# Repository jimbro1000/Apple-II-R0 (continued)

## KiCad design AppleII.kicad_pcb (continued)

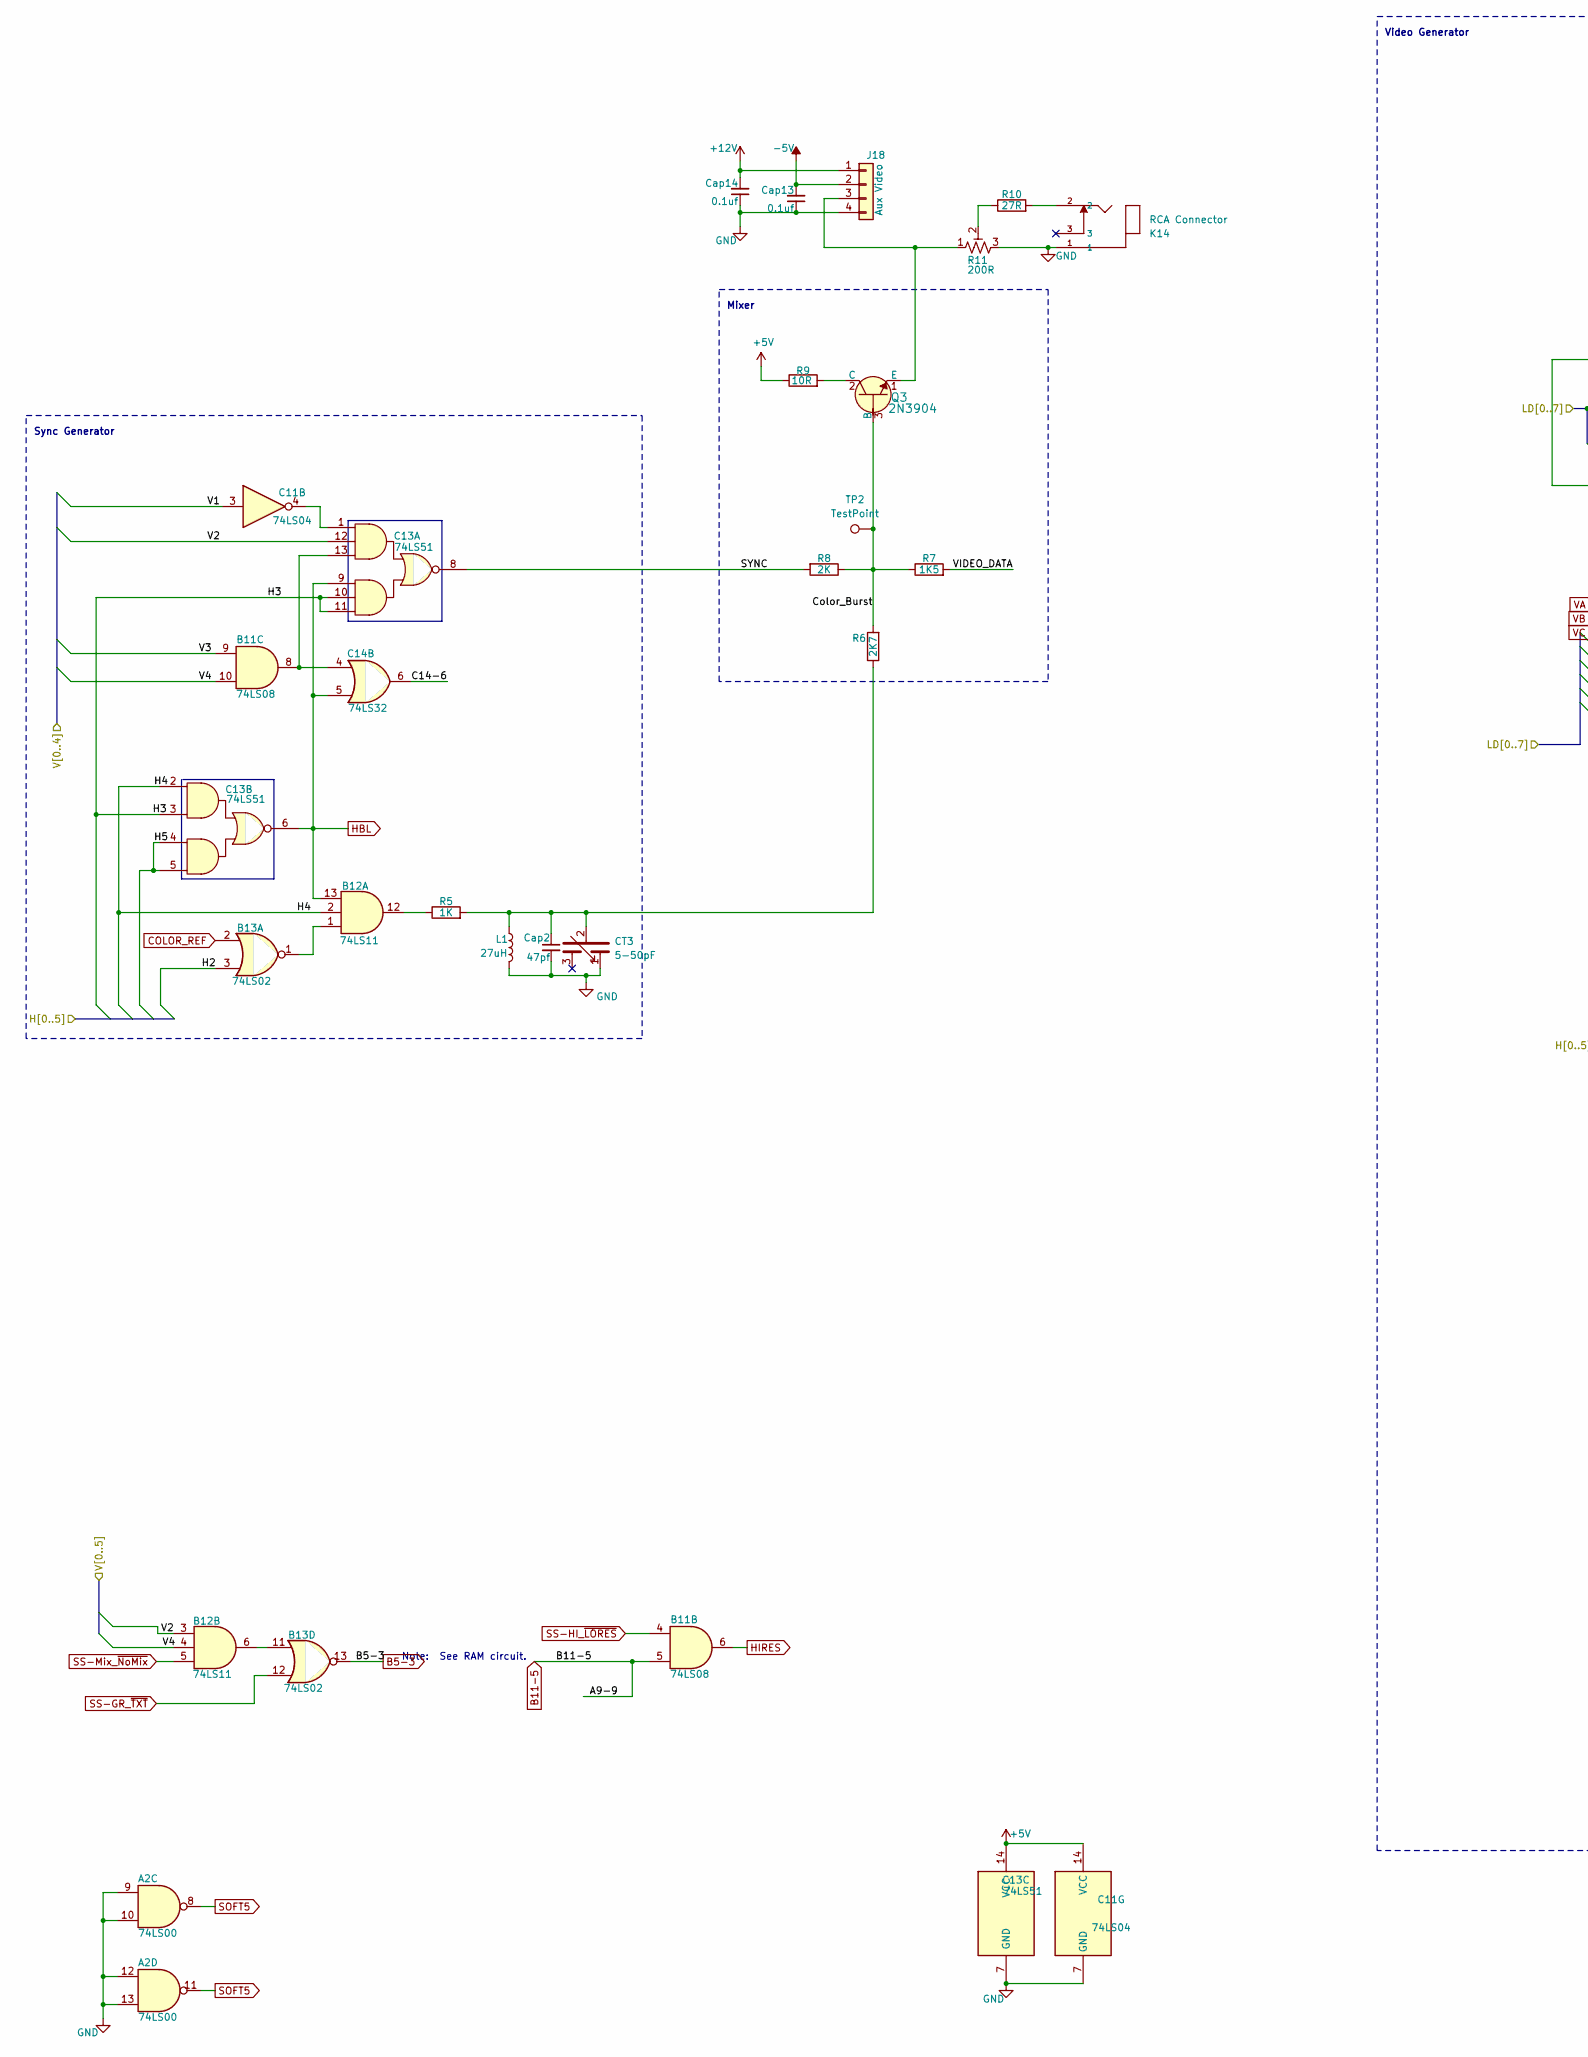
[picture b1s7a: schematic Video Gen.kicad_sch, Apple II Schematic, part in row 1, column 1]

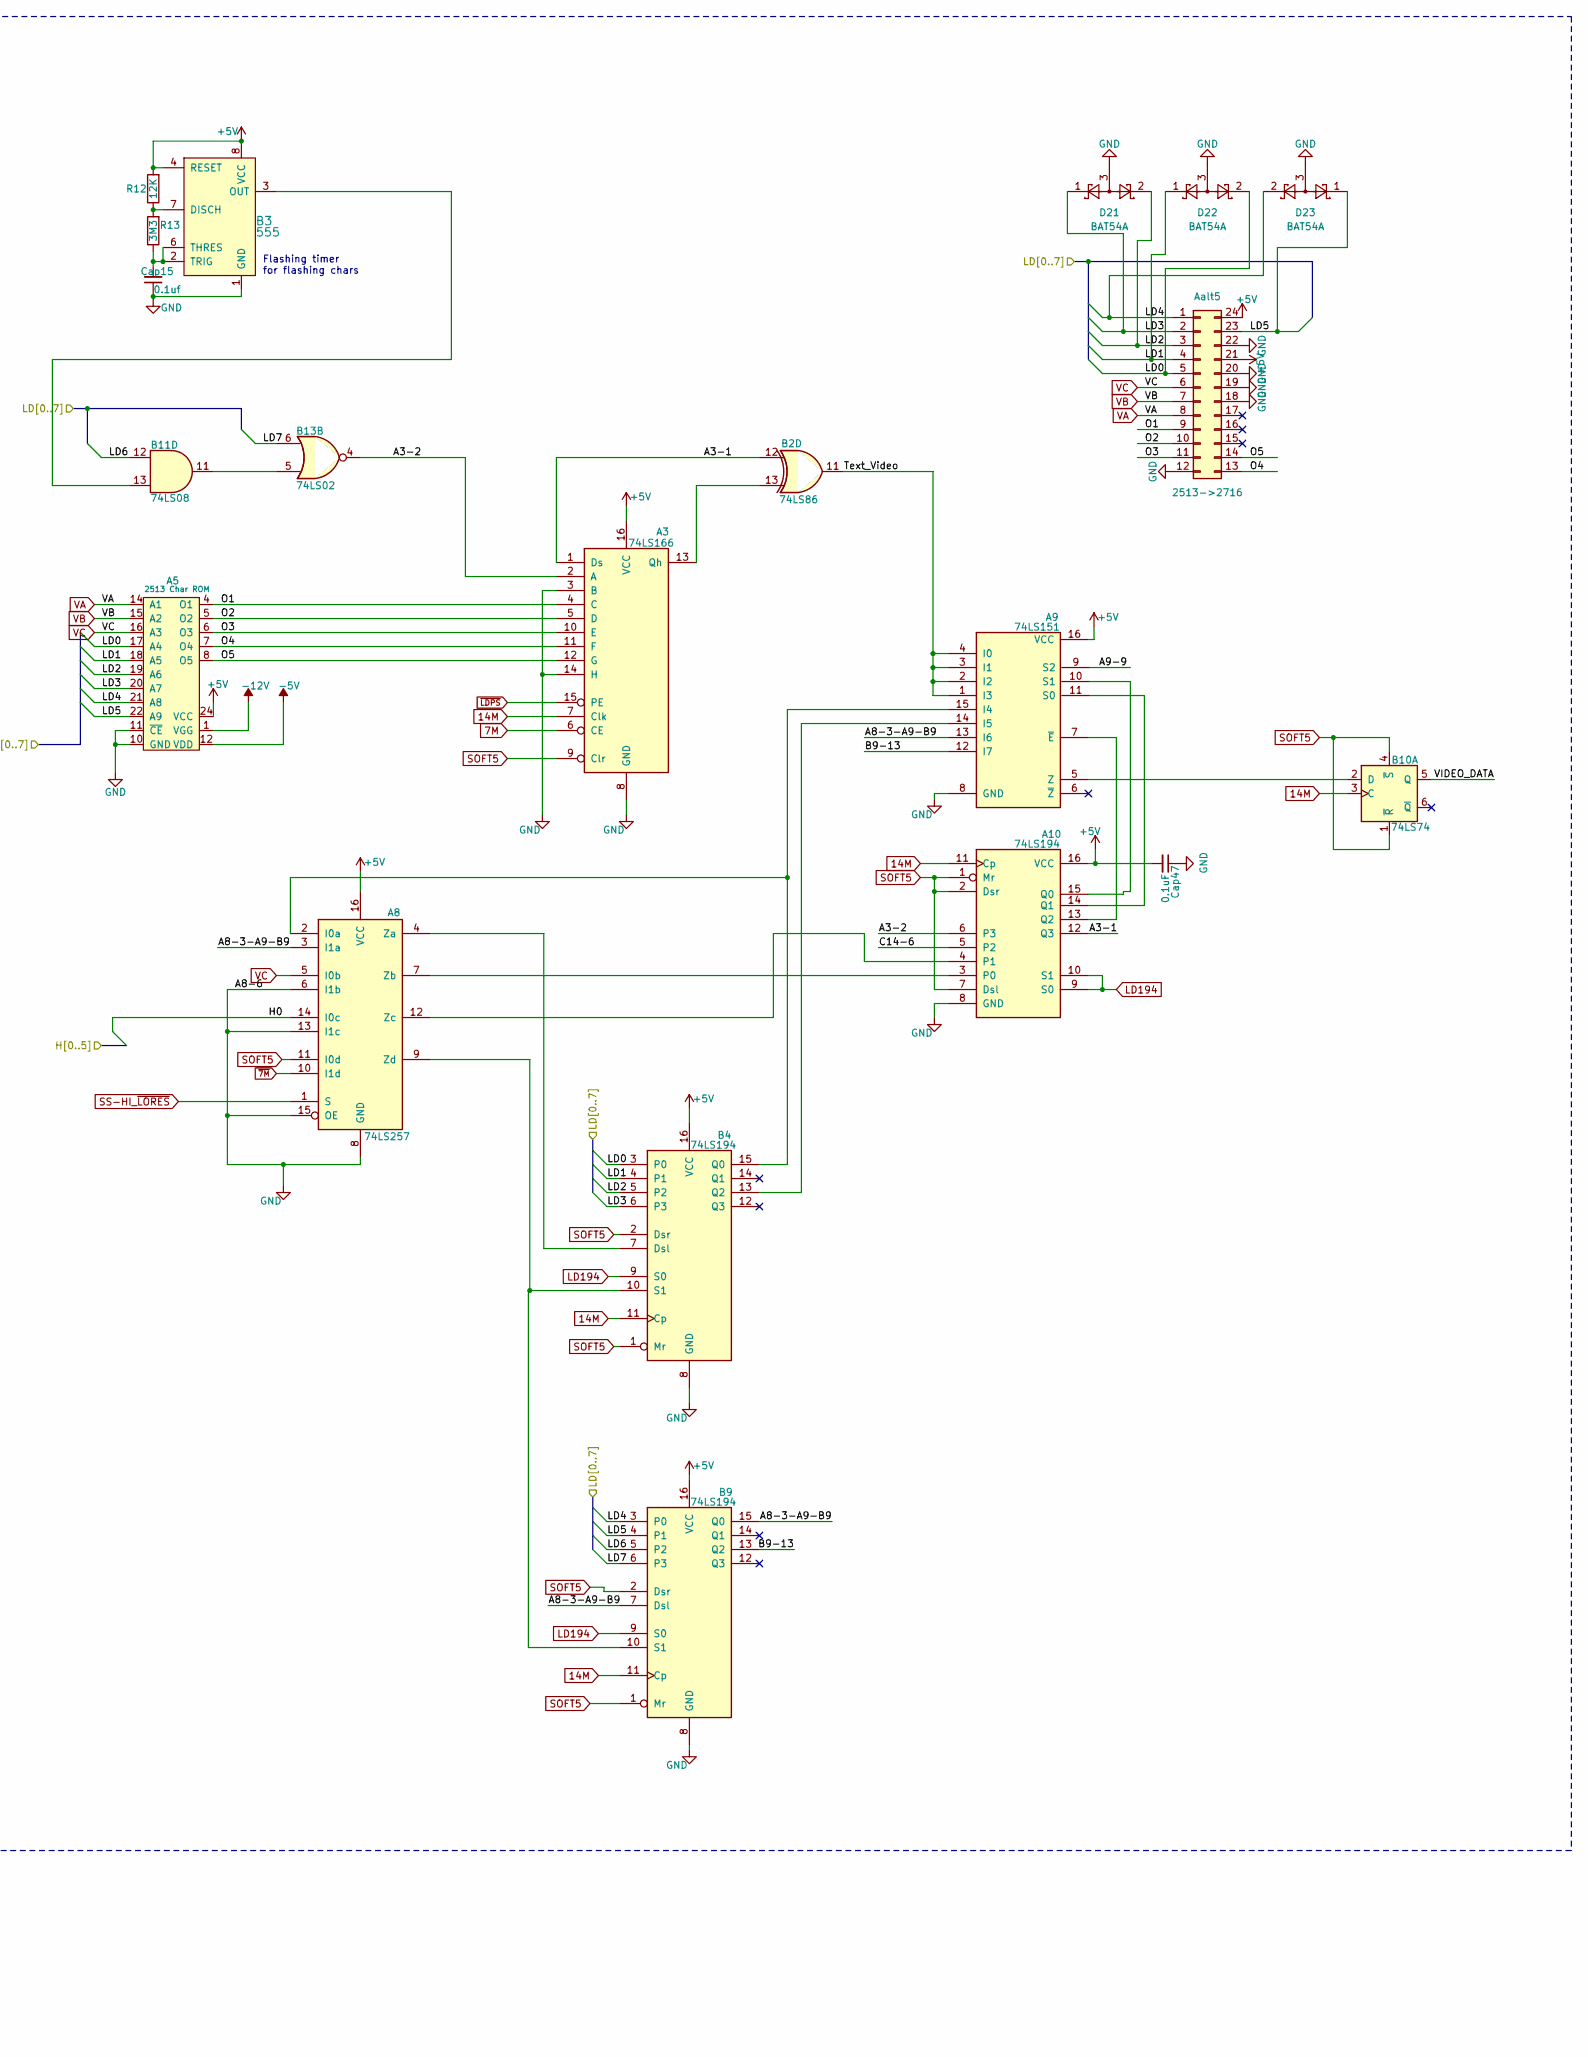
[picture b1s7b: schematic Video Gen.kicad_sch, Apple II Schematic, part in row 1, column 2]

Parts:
A2: 74LS00; DIP-14_W7.62mm
A3: 74LS166; DIP-16_W7.62mm
A5: 2513 Char ROM; DIP-24_W15.24mm
A8: 74LS257; DIP-16_W7.62mm
A9: 74LS151; DIP-16_W7.62mm
A10: 74LS194; DIP-16_W7.62mm
Aalt5: 2513->2716; DIP-24_W15.24mm_Socket
B2: 74LS86; DIP-14_W7.62mm
B3: 555; DIP-8_W7.62mm; MPN NE555P; Digi-Key_PN 296-1411-5-ND
B4, B9: 74LS194; DIP-16_W7.62mm
B10: 74LS74; DIP-14_W7.62mm
B11: 74LS08; DIP-14_W7.62mm
B12: 74LS11; DIP-14_W7.62mm
B13: 74LS02; DIP-14_W7.62mm
C11: 74LS04; DIP-14_W7.62mm
C13: 74LS51; DIP-14_W7.62mm
C14: 74LS32; DIP-14_W7.62mm
CT3: 5-50pF; COLOUR_TRIM; DigiKey BFC280831659-ND
Cap2: 47pf; C_Disc_D7.0mm_W2.5mm_P5.00mm
Cap13, Cap14, Cap15: 0.1uf; C_Disc_D5.0mm_W2.5mm_P5.00mm
Cap47: 0.1uF; C_Disc_D5.0mm_W2.5mm_P5.00mm
D21, D22, D23: BAT54A; SOT-23
J18: Aux Video; PinHeader_1x04_P2.54mm_Vertical
K14: RCA Connector; VIDEO; DigiKey PJRAN1X1U03X-ND
L1: 27uH; L_Axial_L7.0mm_D3.3mm_P12.70mm_Horizontal_Fastron_MICC
Q3: 2N3904; TO-92; MPN 2N3904; Digi-Key_PN 2N3904CS-ND
R5: 1K; R_Axial_DIN0207_L6.3mm_D2.5mm_P10.16mm_Horizontal
R6: 2K7; R_Axial_DIN0207_L6.3mm_D2.5mm_P10.16mm_Horizontal
R7: 1K5; R_Axial_DIN0207_L6.3mm_D2.5mm_P10.16mm_Horizontal
R8: 2K; R_Axial_DIN0207_L6.3mm_D2.5mm_P10.16mm_Horizontal
R9: 10R; R_Axial_DIN0207_L6.3mm_D2.5mm_P10.16mm_Horizontal
R10: 27R; R_Axial_DIN0207_L6.3mm_D2.5mm_P10.16mm_Horizontal
R11: 200R; Potentiometer_Bourns_3266Y_Vertical
R12: 12K; R_Axial_DIN0207_L6.3mm_D2.5mm_P10.16mm_Horizontal
R13: 3M3; R_Axial_DIN0207_L6.3mm_D2.5mm_P10.16mm_Horizontal
TP2: TestPoint; TestPoint_THTPad_1.5x1.5mm_Drill0.7mm

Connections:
7M: A3.6 (CE); also elsewhere on the board
14M: A3.7 (Clk), A10.11 (Cp), B4.11 (Cp), B9.11 (Cp), B10.3 (C); also elsewhere on the board
+5V: A3.16 (VCC), A5.24 (VCC), A8.16 (VCC), A9.16 (VCC), A10.16 (VCC), Aalt5.21, Aalt5.24, B3.4 (RESET), B3.8 (VCC), B4.16 (VCC), B9.16 (VCC), C11.14 (VCC), C13.14 (VCC), Cap47.2, R9.1, R12.2; also elsewhere on the board
+12V: Cap14.2, J18.1; also elsewhere on the board
-5V: A5.12 (VDD), Cap13.2, J18.2; also elsewhere on the board
-12V: A5.1 (VGG); also elsewhere on the board
/CPU Tranceiver Driver and Data MUX/LD0: A5.17 (A4), Aalt5.5, B4.3 (P0), D22.2; also elsewhere on the board
/CPU Tranceiver Driver and Data MUX/LD1: A5.18 (A5), Aalt5.4, B4.4 (P1), D22.1; also elsewhere on the board
/CPU Tranceiver Driver and Data MUX/LD2: A5.19 (A6), Aalt5.3, B4.5 (P2), D21.2; also elsewhere on the board
/CPU Tranceiver Driver and Data MUX/LD3: A5.20 (A7), Aalt5.2, B4.6 (P3), D21.1; also elsewhere on the board
/CPU Tranceiver Driver and Data MUX/LD4: A5.21 (A8), Aalt5.1, B9.3 (P0), D23.2; also elsewhere on the board
/CPU Tranceiver Driver and Data MUX/LD5: A5.22 (A9), Aalt5.23, B9.4 (P1), D23.1; also elsewhere on the board
/CPU Tranceiver Driver and Data MUX/LD6: B9.5 (P2), B11.12; also elsewhere on the board
/CPU Tranceiver Driver and Data MUX/LD7: B9.6 (P3), B13.6; also elsewhere on the board
/Clock Generation/H0: A8.14 (I0c); also elsewhere on the board
/Clock Generation/H2: B13.3; also elsewhere on the board
/Clock Generation/H3: C13.3, C13.10, C13.11; also elsewhere on the board
/Clock Generation/H4: B12.2, C13.2; also elsewhere on the board
/Clock Generation/H5: C13.4, C13.5; also elsewhere on the board
/Clock Generation/V1: C11.3; also elsewhere on the board
/Clock Generation/V2: B12.3, C13.12; also elsewhere on the board
/Clock Generation/V3: B11.9; also elsewhere on the board
/Clock Generation/V4: B11.10, B12.4; also elsewhere on the board
/Video Generation/A3-1: A3.1 (Ds), A10.12 (Q3), B2.12
/Video Generation/A3-2: A3.2 (A), A10.6 (P3), B13.4
/Video Generation/A8-3-A9-B9: A8.3 (I1a), A9.13 (I6), B9.7 (Dsl), B9.15 (Q0)
/Video Generation/B9-13: A9.12 (I7), B9.13 (Q2)
/Video Generation/C14-6: A10.5 (P2), C14.6
/Video Generation/Color_Burst: Q3.3 (B), R6.2, R7.1, R8.1, TP2.1
/Video Generation/SYNC: C13.8, R8.2
/Video Generation/Text_Video: A9.1 (I3), A9.2 (I2), A9.3 (I1), A9.4 (I0), B2.11
/Video Generation/VIDEO_DATA: B10.5 (Q), R7.2
B5-3: B13.13; also elsewhere on the board
B11-5: A9.9 (S2), B11.5; also elsewhere on the board
COLOR_REF: B13.2; also elsewhere on the board
GND: A2.9, A2.10, A2.12, A2.13, A3.3 (B), A3.8 (GND), A3.14 (H), A5.10 (GND), A5.11 (~CE), A8.6 (I1b), A8.8 (GND), A8.13 (I1c), A8.15 (OE), A9.8 (GND), A10.8 (GND), Aalt5.12, Aalt5.18, Aalt5.19, Aalt5.20, Aalt5.22, B3.1 (GND), B4.8 (GND), B9.8 (GND), C11.7 (GND), C13.7 (GND), CT3.1, Cap2.2, Cap13.1, Cap14.1, Cap15.1, Cap47.1, D21.3, D22.3, D23.3, J18.4, K14.1, L1.2, R11.3; also elsewhere on the board
HBL: B12.13, C13.6, C13.9, C14.5; also elsewhere on the board
HIRES: B11.6; also elsewhere on the board
LD194: A10.9 (S0), A10.10 (S1), B4.9 (S0), B9.9 (S0); also elsewhere on the board
unnamed: A3.4 (C), A5.4 (O1), Aalt5.9
unnamed: A3.5 (D), A5.5 (O2), Aalt5.10
unnamed: A3.10 (E), A5.6 (O3), Aalt5.11
unnamed: A3.11 (F), A5.7 (O4), Aalt5.13
unnamed: A3.12 (G), A5.8 (O5), Aalt5.14
unnamed: A3.13 (Qh), B2.13
unnamed: A8.2 (I0a), A9.15 (I4), B4.15 (Q0)
unnamed: A8.4 (Za), B4.7 (Dsl)
unnamed: A8.9 (Zd), B4.10 (S1), B9.10 (S1)
unnamed: A9.14 (I5), B4.13 (Q2)
unnamed: A9.5 (Z), B10.2 (D)
unnamed: A8.7 (Zb), A10.3 (P0)
unnamed: A8.12 (Zc), A10.4 (P1)
unnamed: A9.10 (S1), A10.15 (Q0)
unnamed: A9.11 (S0), A10.14 (Q1)
unnamed: A9.7 (~E), A10.13 (Q2)
unnamed: B3.7 (DISCH), R12.1, R13.2
unnamed: B3.3 (OUT), B11.13
unnamed: B3.2 (TRIG), B3.6 (THRES), Cap15.2, R13.1
unnamed: B11.8, C13.13, C14.4
unnamed: B11.11, B13.5
unnamed: B12.1, B13.1
unnamed: B12.6, B13.11
unnamed: B12.12, R5.1
unnamed: C11.4, C13.1
unnamed: CT3.2, Cap2.1, L1.1, R5.2, R6.1
unnamed: J18.3, Q3.1 (E), R11.1
unnamed: K14.2, R10.2
unnamed: Q3.2 (C), R9.2
unnamed: R10.1, R11.2
SOFT5: A2.8, A2.11, A3.9 (Clr), A8.11 (I0d), A10.1 (Mr), A10.2 (Dsr), A10.7 (Dsl), B4.1 (Mr), B4.2 (Dsr), B9.1 (Mr), B9.2 (Dsr), B10.1 (~R), B10.4 (~S); also elsewhere on the board
SS-GR_~TXT: B13.12; also elsewhere on the board
SS-HI_~LORES: A8.1 (S), B11.4; also elsewhere on the board
SS-Mix_~NoMix: B12.5; also elsewhere on the board
VA: A5.14 (A1), Aalt5.8; also elsewhere on the board
VB: A5.15 (A2), Aalt5.7; also elsewhere on the board
VC: A5.16 (A3), A8.5 (I0b), Aalt5.6; also elsewhere on the board
~7M: A8.10 (I1d); also elsewhere on the board
~LDPS: A3.15 (PE); also elsewhere on the board

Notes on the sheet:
Flashing timer for flashing chars
Note: See RAM circuit.
Sync Generator
Mixer
Video Generator

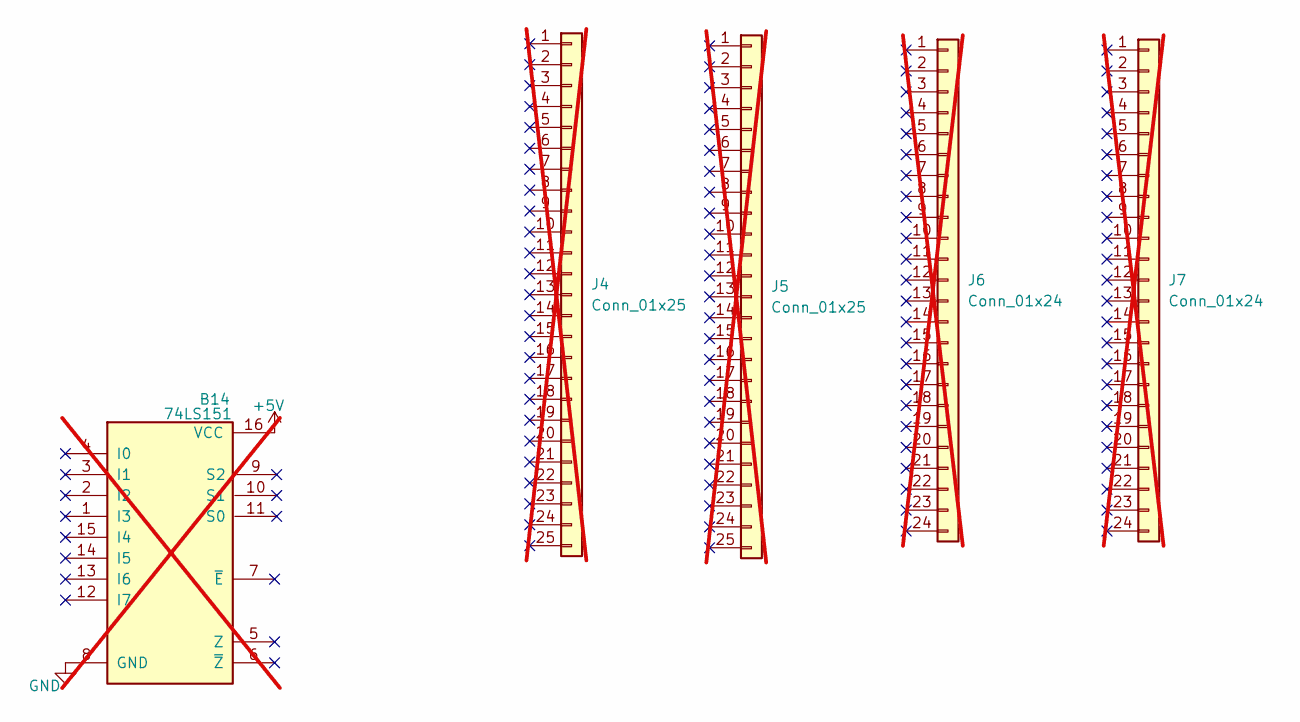
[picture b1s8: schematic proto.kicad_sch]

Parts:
B14: 74LS151; DIP-16_W7.62mm_Socket_LongPads; not fitted
J4, J5: Conn_01x25; SIP-25; not fitted
J6, J7: Conn_01x24; SIP-24; not fitted

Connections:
+5V: B14.16 (VCC); also elsewhere on the board
GND: B14.8 (GND); also elsewhere on the board

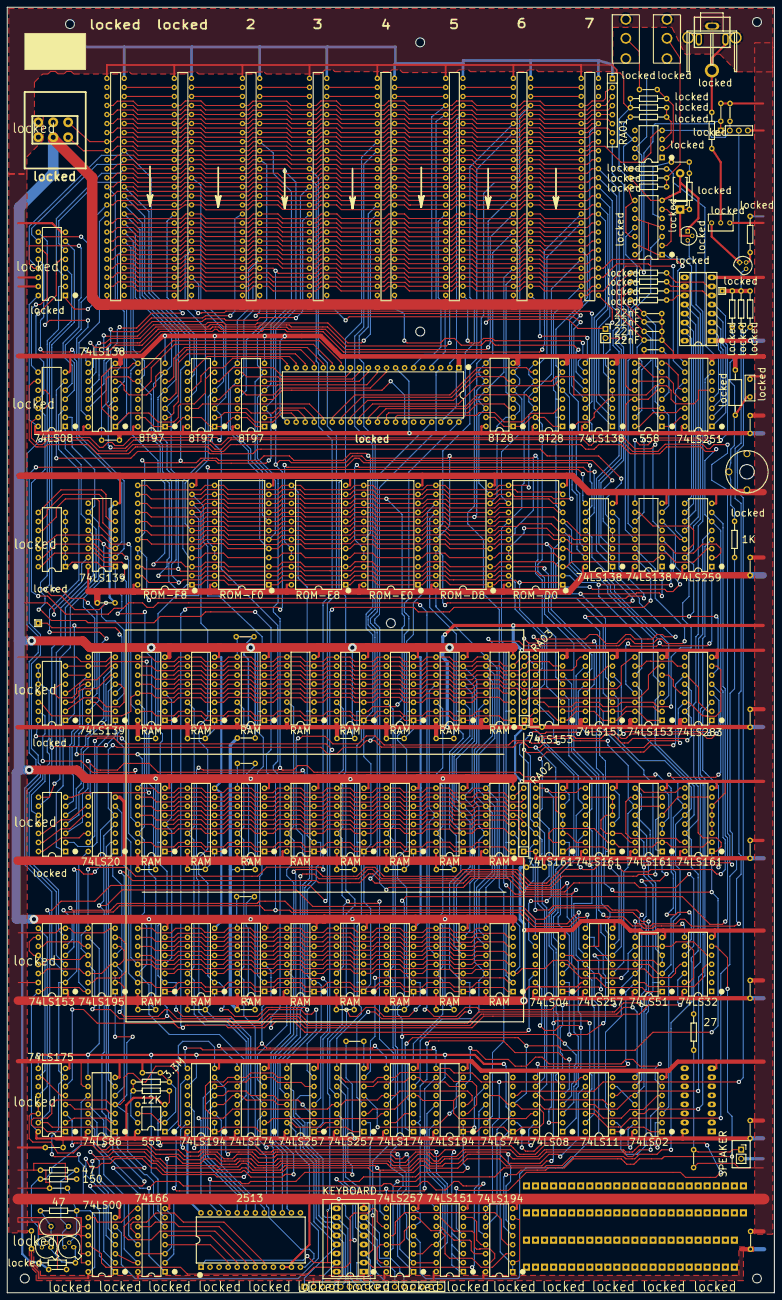
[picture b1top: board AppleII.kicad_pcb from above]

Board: 2 copper layers, 215.5 x 361.2 mm, 203 parts (0 on the bottom side), 317 nets.

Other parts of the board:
CP0: Power Connector; POWER
MH1, MH2, MH3, MH4, MH5, MH6, MH7: MountingHole; MountingHole_2.5mm
SLOT0, SLOT1, SLOT2, SLOT3, SLOT4, SLOT5, SLOT6, SLOT7: 50 pin slot; Standard_Edge_Connector
TP1: TestPoint; TestPoint_THTPad_1.5x1.5mm_Drill0.7mm

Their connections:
7M: SLOT0.36, SLOT1.36, SLOT2.36, SLOT3.36, SLOT4.36, SLOT5.36, SLOT6.36, SLOT7.36; also elsewhere on the board
+5V: CP0.3, SLOT0.25, SLOT1.25, SLOT2.25, SLOT3.25, SLOT4.25, SLOT5.25, SLOT6.25, SLOT7.25; also elsewhere on the board
+12V: CP0.4, SLOT0.50, SLOT1.50, SLOT2.50, SLOT3.50, SLOT4.50, SLOT5.50, SLOT6.50, SLOT7.50; also elsewhere on the board
-5V: CP0.6, SLOT0.34, SLOT1.34, SLOT2.34, SLOT3.34, SLOT4.34, SLOT5.34, SLOT6.34, SLOT7.34; also elsewhere on the board
-12V: CP0.5, SLOT0.33, SLOT1.33, SLOT2.33, SLOT3.33, SLOT4.33, SLOT5.33, SLOT6.33, SLOT7.33; also elsewhere on the board
/Connectors/DMA-OUT-3: SLOT3.24, SLOT4.27
/Connectors/INT-OUT-3: SLOT3.23, SLOT4.28
A0: SLOT0.2, SLOT1.2, SLOT2.2, SLOT3.2, SLOT4.2, SLOT5.2, SLOT6.2, SLOT7.2; also elsewhere on the board
A1: SLOT0.3, SLOT1.3, SLOT2.3, SLOT3.3, SLOT4.3, SLOT5.3, SLOT6.3, SLOT7.3; also elsewhere on the board
A2: SLOT0.4, SLOT1.4, SLOT2.4, SLOT3.4, SLOT4.4, SLOT5.4, SLOT6.4, SLOT7.4; also elsewhere on the board
A3: SLOT0.5, SLOT1.5, SLOT2.5, SLOT3.5, SLOT4.5, SLOT5.5, SLOT6.5, SLOT7.5; also elsewhere on the board
A4: SLOT0.6, SLOT1.6, SLOT2.6, SLOT3.6, SLOT4.6, SLOT5.6, SLOT6.6, SLOT7.6; also elsewhere on the board
A5: SLOT0.7, SLOT1.7, SLOT2.7, SLOT3.7, SLOT4.7, SLOT5.7, SLOT6.7, SLOT7.7; also elsewhere on the board
A6: SLOT0.8, SLOT1.8, SLOT2.8, SLOT3.8, SLOT4.8, SLOT5.8, SLOT6.8, SLOT7.8; also elsewhere on the board
A7: SLOT0.9, SLOT1.9, SLOT2.9, SLOT3.9, SLOT4.9, SLOT5.9, SLOT6.9, SLOT7.9; also elsewhere on the board
A8: SLOT0.10, SLOT1.10, SLOT2.10, SLOT3.10, SLOT4.10, SLOT5.10, SLOT6.10, SLOT7.10; also elsewhere on the board
A9: SLOT0.11, SLOT1.11, SLOT2.11, SLOT3.11, SLOT4.11, SLOT5.11, SLOT6.11, SLOT7.11; also elsewhere on the board
A10: SLOT0.12, SLOT1.12, SLOT2.12, SLOT3.12, SLOT4.12, SLOT5.12, SLOT6.12, SLOT7.12; also elsewhere on the board
A11: SLOT0.13, SLOT1.13, SLOT2.13, SLOT3.13, SLOT4.13, SLOT5.13, SLOT6.13, SLOT7.13; also elsewhere on the board
A12: SLOT0.14, SLOT1.14, SLOT2.14, SLOT3.14, SLOT4.14, SLOT5.14, SLOT6.14, SLOT7.14; also elsewhere on the board
A13: SLOT0.15, SLOT1.15, SLOT2.15, SLOT3.15, SLOT4.15, SLOT5.15, SLOT6.15, SLOT7.15; also elsewhere on the board
A14: SLOT0.16, SLOT1.16, SLOT2.16, SLOT3.16, SLOT4.16, SLOT5.16, SLOT6.16, SLOT7.16; also elsewhere on the board
A15: SLOT0.17, SLOT1.17, SLOT2.17, SLOT3.17, SLOT4.17, SLOT5.17, SLOT6.17, SLOT7.17; also elsewhere on the board
D0: SLOT0.49, SLOT1.49, SLOT2.49, SLOT3.49, SLOT4.49, SLOT5.49, SLOT6.49, SLOT7.49; also elsewhere on the board
D1: SLOT0.48, SLOT1.48, SLOT2.48, SLOT3.48, SLOT4.48, SLOT5.48, SLOT6.48, SLOT7.48; also elsewhere on the board
D2: SLOT0.47, SLOT1.47, SLOT2.47, SLOT3.47, SLOT4.47, SLOT5.47, SLOT6.47, SLOT7.47; also elsewhere on the board
D3: SLOT0.46, SLOT1.46, SLOT2.46, SLOT3.46, SLOT4.46, SLOT5.46, SLOT6.46, SLOT7.46; also elsewhere on the board
D4: SLOT0.45, SLOT1.45, SLOT2.45, SLOT3.45, SLOT4.45, SLOT5.45, SLOT6.45, SLOT7.45; also elsewhere on the board
D5: SLOT0.44, SLOT1.44, SLOT2.44, SLOT3.44, SLOT4.44, SLOT5.44, SLOT6.44, SLOT7.44; also elsewhere on the board
D6: SLOT0.43, SLOT1.43, SLOT2.43, SLOT3.43, SLOT4.43, SLOT5.43, SLOT6.43, SLOT7.43; also elsewhere on the board
D7: SLOT0.42, SLOT1.42, SLOT2.42, SLOT3.42, SLOT4.42, SLOT5.42, SLOT6.42, SLOT7.42; also elsewhere on the board
GND: CP0.1, CP0.2, SLOT0.26, SLOT1.26, SLOT2.26, SLOT3.26, SLOT4.26, SLOT5.26, SLOT6.26, SLOT7.26; also elsewhere on the board
NC1: SLOT0.19, SLOT1.19, SLOT2.19, SLOT3.19, SLOT4.19, SLOT5.19, SLOT6.19, SLOT7.19
NC2: SLOT0.35, SLOT1.35, SLOT2.35, SLOT3.35, SLOT4.35, SLOT5.35, SLOT6.35, SLOT7.35
unnamed 186: TP1.1; also elsewhere on the board
unnamed: SLOT0.23, SLOT1.28
unnamed: SLOT0.24, SLOT1.27
unnamed: SLOT1.23, SLOT2.28
unnamed: SLOT1.24, SLOT2.27
unnamed: SLOT2.23, SLOT3.28
unnamed: SLOT2.24, SLOT3.27
unnamed: SLOT4.23, SLOT5.28
unnamed: SLOT4.24, SLOT5.27
unnamed: SLOT5.23, SLOT6.28
unnamed: SLOT5.24, SLOT6.27
unnamed: SLOT6.23, SLOT7.28
unnamed: SLOT6.24, SLOT7.27
PHI0: SLOT0.40, SLOT1.40, SLOT2.40, SLOT3.40, SLOT4.40, SLOT5.40, SLOT6.40, SLOT7.40; also elsewhere on the board
PHI1: SLOT0.38, SLOT1.38, SLOT2.38, SLOT3.38, SLOT4.38, SLOT5.38, SLOT6.38, SLOT7.38; also elsewhere on the board
Q3: SLOT0.37, SLOT1.37, SLOT2.37, SLOT3.37, SLOT4.37, SLOT5.37, SLOT6.37, SLOT7.37; also elsewhere on the board
RDY: SLOT0.21, SLOT1.21, SLOT2.21, SLOT3.21, SLOT4.21, SLOT5.21, SLOT6.21, SLOT7.21; also elsewhere on the board
R~W: SLOT0.18, SLOT1.18, SLOT2.18, SLOT3.18, SLOT4.18, SLOT5.18, SLOT6.18, SLOT7.18; also elsewhere on the board
USER-1: SLOT0.39, SLOT1.39, SLOT2.39, SLOT3.39, SLOT4.39, SLOT5.39, SLOT6.39, SLOT7.39; also elsewhere on the board
~DEV-SEL-0: SLOT0.41; also elsewhere on the board
~DEV-SEL-1: SLOT1.41; also elsewhere on the board
~DEV-SEL-2: SLOT2.41; also elsewhere on the board
~DEV-SEL-3: SLOT3.41; also elsewhere on the board
~DEV-SEL-4: SLOT4.41; also elsewhere on the board
~DEV-SEL-5: SLOT5.41; also elsewhere on the board
~DEV-SEL-6: SLOT6.41; also elsewhere on the board
~DEV-SEL-7: SLOT7.41; also elsewhere on the board
~DMA: SLOT0.22, SLOT1.22, SLOT2.22, SLOT3.22, SLOT4.22, SLOT5.22, SLOT6.22, SLOT7.22; also elsewhere on the board
~INH: SLOT0.32, SLOT1.32, SLOT2.32, SLOT3.32, SLOT4.32, SLOT5.32, SLOT6.32, SLOT7.32; also elsewhere on the board
~IO-SELECT-1: SLOT1.1; also elsewhere on the board
~IO-SELECT-2: SLOT2.1; also elsewhere on the board
~IO-SELECT-3: SLOT3.1; also elsewhere on the board
~IO-SELECT-4: SLOT4.1; also elsewhere on the board
~IO-SELECT-5: SLOT5.1; also elsewhere on the board
~IO-SELECT-6: SLOT6.1; also elsewhere on the board
~IO-SELECT-7: SLOT7.1; also elsewhere on the board
~IO_STB: SLOT0.20, SLOT1.20, SLOT2.20, SLOT3.20, SLOT4.20, SLOT5.20, SLOT6.20, SLOT7.20; also elsewhere on the board
~IRQ: SLOT0.30, SLOT1.30, SLOT2.30, SLOT3.30, SLOT4.30, SLOT5.30, SLOT6.30, SLOT7.30; also elsewhere on the board
~NMI: SLOT0.29, SLOT1.29, SLOT2.29, SLOT3.29, SLOT4.29, SLOT5.29, SLOT6.29, SLOT7.29; also elsewhere on the board
~RESET: SLOT0.31, SLOT1.31, SLOT2.31, SLOT3.31, SLOT4.31, SLOT5.31, SLOT6.31, SLOT7.31; also elsewhere on the board

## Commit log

2024-01-28 update traces
2024-01-29 more traces
2024-01-29 more tracing
2024-01-30 more traces and nicer text
2024-01-30 more tracing - down to row E
2024-01-31 finish tracing
2024-02-01 beautify capacitor footprint
2024-02-01 add readme
2024-02-01 Revert "add readme"
    This reverts commit 634f48f07a63fbb27ccd8abdd91f3bb91a3d29dd.
2024-02-01 beautify resistors
2024-02-01 restore README
2024-02-01 more beautifaction
2024-02-01 add ibom
2024-02-02 fix H14 pin 6
2024-02-02 complete beautification
2024-02-02 generate bom
2024-02-04 add missing test points
2024-02-12 add alternative char gen footprint
2024-02-12 fix assignment of LD0-7 net
